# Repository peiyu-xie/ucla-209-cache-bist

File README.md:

# ucla-209-cache-bist

A 32x128-bit fully associative cache with single-cycle CAM tag lookup and an
LFSR/MISR built-in self-test (BIST) engine, taken from RTL to GDSII in 180nm
CMOS and taped out — plus the FPGA tester built to bring the chip up in the
lab. UCLA EC ENGR 209AS/209BS (tapeout course sequence), 2026.

## The chip

| Block | File | What it does |
|---|---|---|
| Cache | `rtl/Cache.sv` | 32 entries x 128-bit data; a CAM priority engine compares every tag in parallel in one cycle |
| BIST controller | `rtl/BIST_Controller.sv` | FSM that sequences write and compare phases over the whole array |
| Test-pattern generator | `rtl/TPG.sv` | LFSR producing pseudo-random write data and addresses |
| Response compactor | `rtl/MISR.sv` | 129-bit multiple-input signature register; the final signature is the pass/fail check |
| Serial I/O | `rtl/P2S.sv`, `rtl/S2P.sv`, `rtl/bidirectional_P2S_S2P.sv` | Moves 128-bit words through the pin-limited pad frame |
| Top | `rtl/Cache_BIST_Top.sv`, `rtl/Chip.sv` | Integration and pad-level top |

**Verification.** Unit- and chip-level SystemVerilog testbenches (`*_tb.sv`)
with randomized address/data stimulus, plus `Chip_post_sim_tb.sv`, a
post-layout gate-level simulation back-annotated with SDF from Innovus.

**Implementation.** Hammer-driven Genus synthesis and Innovus place and route
(MMMC setup in `flow/mmmc_ori.tcl`), DRC/LVS, and post-layout parasitic
extraction before tapeout sign-off.

## The tester (`tester/`)

Silicon validation runs on a Xilinx Zynq board (PYNQ-Z2, `xc7z020clg400-1`).

- **`bus_sequencer.sv`** — 14-state FSM that owns the DUT clock and all
  protocol timing: reset, RUN_BIST, write, compare, and read with bus
  turnaround for the bidirectional data pins. It runs *in the DUT clock
  domain*, so read/write transactions stay cycle-accurate at any test
  frequency, up to the 95 MHz MMCM clock.
- **`tester_top.sv`** — clocking and transport: a 95 MHz MMCM and a
  programmable divider switched glitch-free by a BUFGMUX, the DUT clock
  forwarded off-chip through an ODDR, IOBUFs for the bidirectional bus, and
  synchronizers on the clock-domain crossings of the register interface.
- **`register_map.md`** — the PC-to-FPGA register contract (CTRL, STATUS,
  CLKDIV, ADDR, WDATA0-3, RDATA0-3, ...).
- **`TEST_PROCEDURE.md`** — step-by-step bring-up, first against a chip
  emulator, then against silicon with the same bitstream and commands.
- `tester_top.xdc`, `xdc/chip_emulator.xdc`, `stage1.tcl` — pin constraints and
  Vivado build script.

See `tester/README.md` for build instructions.

## Not included

- `Chip_ckt.v` — Innovus post-layout netlist; it instantiates TSMC standard
  cells (foundry PDK, NDA).
- Course handouts, pad-frame and tapeout documents (instructor / foundry material).
- The chip carrier PCB, which my project partner designed; the tester drives
  its level shifters through `shifter_oe_n` / `shifter_dir`.
- Generated build outputs (bitstreams, Vivado runs).

---

Author: Pei-yu Xie

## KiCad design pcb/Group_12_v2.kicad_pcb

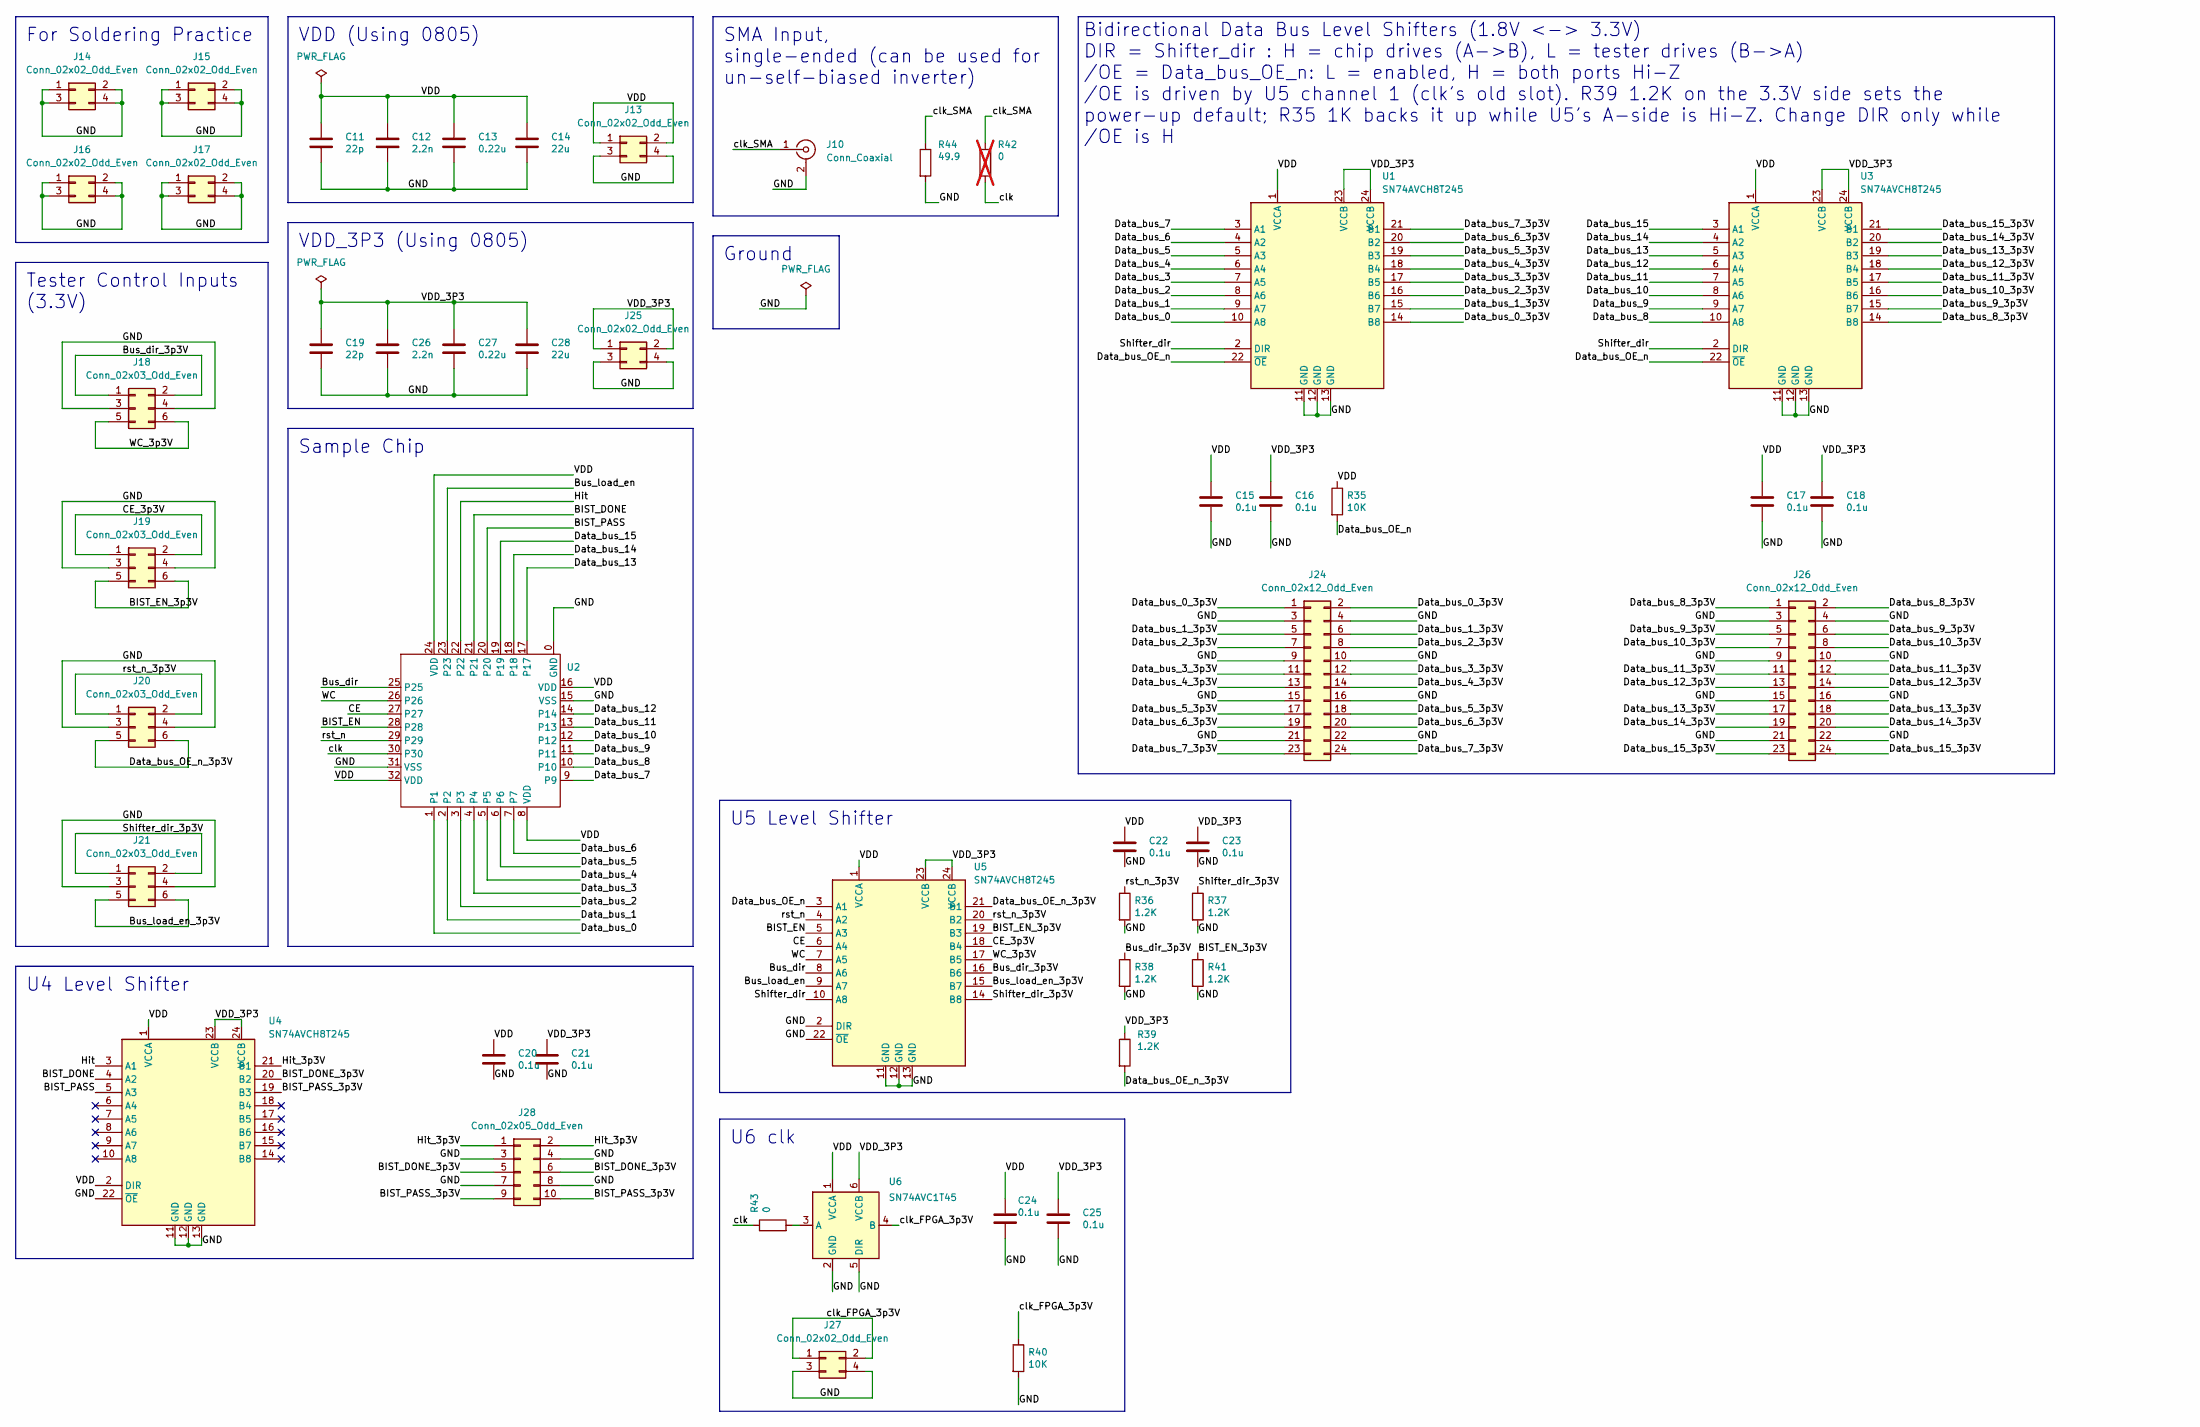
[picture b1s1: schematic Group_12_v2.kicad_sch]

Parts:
C11, C19: 22p; C_0805_2012Metric_Pad1.18x1.45mm_HandSolder; LCSC Part # C1804
C12, C26: 2.2n; C_0805_2012Metric_Pad1.18x1.45mm_HandSolder; LCSC Part # C28260
C13, C27: 0.22u; C_0805_2012Metric_Pad1.18x1.45mm_HandSolder; LCSC Part # C5378
C14, C28: 22u; C_0805_2012Metric_Pad1.18x1.45mm_HandSolder; LCSC Part # C45783
C15, C16, C17, C18, C20, C21, C22, C23, C24, C25: 0.1u; C_0805_2012Metric_Pad1.18x1.45mm_HandSolder; LCSC Part # C1711
J10: Conn_Coaxial; SMA_Samtec_SMA-J-P-H-ST-EM1_EdgeMount
J13, J14, J15, J16, J17, J25, J27: Conn_02x02_Odd_Even; PinHeader_2x02_P2.54mm_Vertical
J18, J19, J20, J21: Conn_02x03_Odd_Even; PinHeader_2x03_P2.54mm_Vertical
J24, J26: Conn_02x12_Odd_Even; PinHeader_2x12_P2.54mm_Vertical
J28: Conn_02x05_Odd_Even; PinHeader_2x05_P2.54mm_Vertical
R35, R40: 10K; R_0805_2012Metric_Pad1.20x1.40mm_HandSolder; LCSC Part # C17414
R36, R37, R38, R39, R41: 1.2K; R_0805_2012Metric_Pad1.20x1.40mm_HandSolder; LCSC Part # C17379
R42: 0; R_0805_2012Metric_Pad1.20x1.40mm_HandSolder; LCSC Part # C17477; not fitted
R43: 0; R_0805_2012Metric_Pad1.20x1.40mm_HandSolder; LCSC Part # C17477
R44: 49.9; R_0805_2012Metric_Pad1.20x1.40mm_HandSolder; LCSC Part # C17720
U1, U3, U4, U5: SN74AVCH8T245; TSSOP-24_4.4x7.8mm_P0.65mm; LCSC Part # C2652945
U2: EE209AS_2026
U6: SN74AVC1T45; SOT-23-6; LCSC Part # C131978

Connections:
/BIST_DONE: U2.21, U4.4 (A2)
/BIST_DONE_3p3V: J28.5, J28.6, U4.20 (B2)
/BIST_EN: U2.28, U5.5 (A3)
/BIST_EN_3p3V: J19.5, J19.6, R41.1, U5.19 (B3)
/BIST_PASS: U2.20, U4.5 (A3)
/BIST_PASS_3p3V: J28.9, J28.10, U4.19 (B3)
/Bus_dir: U2.25, U5.8 (A6)
/Bus_dir_3p3V: J18.1, J18.2, R38.1, U5.16 (B6)
/Bus_load_en: U2.23, U5.9 (A7)
/Bus_load_en_3p3V: J21.5, J21.6, U5.15 (B7)
/CE: U2.27, U5.6 (A4)
/CE_3p3V: J19.1, J19.2, U5.18 (B4)
/Data_bus_0: U1.10 (A8), U2.1
/Data_bus_0_3p3V: J24.1, J24.2, U1.14 (B8)
/Data_bus_1: U1.9 (A7), U2.2
/Data_bus_1_3p3V: J24.5, J24.6, U1.15 (B7)
/Data_bus_2: U1.8 (A6), U2.3
/Data_bus_2_3p3V: J24.7, J24.8, U1.16 (B6)
/Data_bus_3: U1.7 (A5), U2.4
/Data_bus_3_3p3V: J24.11, J24.12, U1.17 (B5)
/Data_bus_4: U1.6 (A4), U2.5
/Data_bus_4_3p3V: J24.13, J24.14, U1.18 (B4)
/Data_bus_5: U1.5 (A3), U2.6
/Data_bus_5_3p3V: J24.17, J24.18, U1.19 (B3)
/Data_bus_6: U1.4 (A2), U2.7
/Data_bus_6_3p3V: J24.19, J24.20, U1.20 (B2)
/Data_bus_7: U1.3 (A1), U2.9
/Data_bus_7_3p3V: J24.23, J24.24, U1.21 (B1)
/Data_bus_8: U2.10, U3.10 (A8)
/Data_bus_8_3p3V: J26.1, J26.2, U3.14 (B8)
/Data_bus_9: U2.11, U3.9 (A7)
/Data_bus_9_3p3V: J26.5, J26.6, U3.15 (B7)
/Data_bus_10: U2.12, U3.8 (A6)
/Data_bus_10_3p3V: J26.7, J26.8, U3.16 (B6)
/Data_bus_11: U2.13, U3.7 (A5)
/Data_bus_11_3p3V: J26.11, J26.12, U3.17 (B5)
/Data_bus_12: U2.14, U3.6 (A4)
/Data_bus_12_3p3V: J26.13, J26.14, U3.18 (B4)
/Data_bus_13: U2.17, U3.5 (A3)
/Data_bus_13_3p3V: J26.17, J26.18, U3.19 (B3)
/Data_bus_14: U2.18, U3.4 (A2)
/Data_bus_14_3p3V: J26.19, J26.20, U3.20 (B2)
/Data_bus_15: U2.19, U3.3 (A1)
/Data_bus_15_3p3V: J26.23, J26.24, U3.21 (B1)
/Data_bus_OE_n: R35.2, U1.22 (~OE), U3.22 (~OE), U5.3 (A1)
/Data_bus_OE_n_3p3V: J20.5, J20.6, R39.2, U5.21 (B1)
/GND: C11.2, C12.2, C13.2, C14.2, C15.2, C16.2, C17.2, C18.2, C19.2, C20.2, C21.2, C22.2, C23.2, C24.2, C25.2, C26.2, C27.2, C28.2, J10.2 (Ext), J13.3, J13.4, J14.1, J14.2, J14.3, J14.4, J15.1, J15.2, J15.3, J15.4, J16.1, J16.2, J16.3, J16.4, J17.1, J17.2, J17.3, J17.4, J18.3, J18.4, J19.3, J19.4, J20.3, J20.4, J21.3, J21.4, J24.3, J24.4, J24.9, J24.10, J24.15, J24.16, J24.21, J24.22, J25.3, J25.4, J26.3, J26.4, J26.9, J26.10, J26.15, J26.16, J26.21, J26.22, J27.3, J27.4, J28.3, J28.4, J28.7, J28.8, R36.2, R37.2, R38.2, R40.2, R41.2, R44.2, U1.11 (GND), U1.12 (GND), U1.13 (GND), U2.0 (GND), U2.15 (VSS), U2.31 (VSS), U3.11 (GND), U3.12 (GND), U3.13 (GND), U4.11 (GND), U4.12 (GND), U4.13 (GND), U4.22 (~OE), U5.2 (DIR), U5.11 (GND), U5.12 (GND), U5.13 (GND), U5.22 (~OE), U6.2 (GND), U6.5 (DIR)
/Hit: U2.22, U4.3 (A1)
/Hit_3p3V: J28.1, J28.2, U4.21 (B1)
/Shifter_dir: U1.2 (DIR), U3.2 (DIR), U5.10 (A8)
/Shifter_dir_3p3V: J21.1, J21.2, R37.1, U5.14 (B8)
/VDD: C11.1, C12.1, C13.1, C14.1, C15.1, C17.1, C20.1, C22.1, C24.1, J13.1, J13.2, R35.1, U1.1 (VCCA), U2.8 (VDD), U2.16 (VDD), U2.24 (VDD), U2.32 (VDD), U3.1 (VCCA), U4.1 (VCCA), U4.2 (DIR), U5.1 (VCCA), U6.1 (VCCA)
/VDD_3P3: C16.1, C18.1, C19.1, C21.1, C23.1, C25.1, C26.1, C27.1, C28.1, J25.1, J25.2, R39.1, U1.23 (VCCB), U1.24 (VCCB), U3.23 (VCCB), U3.24 (VCCB), U4.23 (VCCB), U4.24 (VCCB), U5.23 (VCCB), U5.24 (VCCB), U6.6 (VCCB)
/WC: U2.26, U5.7 (A5)
/WC_3p3V: J18.5, J18.6, U5.17 (B5)
/clk: R42.2, R43.1, U2.30
/clk_FPGA_3p3V: J27.1, J27.2, R40.1, U6.4 (B)
/clk_SMA: J10.1 (In), R42.1, R44.1
/rst_n: U2.29, U5.4 (A2)
/rst_n_3p3V: J20.1, J20.2, R36.1, U5.20 (B2)
unnamed: R43.2, U6.3 (A)

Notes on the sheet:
VDD_3P3 (Using 0805)
VDD (Using 0805)
SMA Input, single-ended (can be used for un-self-biased inverter)
For Soldering Practice
Ground
Sample Chip
U6 clk
U4 Level Shifter
Tester Control Inputs (3.3V)
U5 Level Shifter
Bidirectional Data Bus Level Shifters (1.8V <-> 3.3V) DIR = Shifter_dir : H = chip drives (A->B), L = tester drives (B->A) /OE = Data_bus_OE_n: L = enabled, H = both ports Hi-Z /OE is driven by U5 channel 1 (clk's old slot). R39 1.2K on the 3.3V side sets the power-up default; R35 1K backs it up wh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

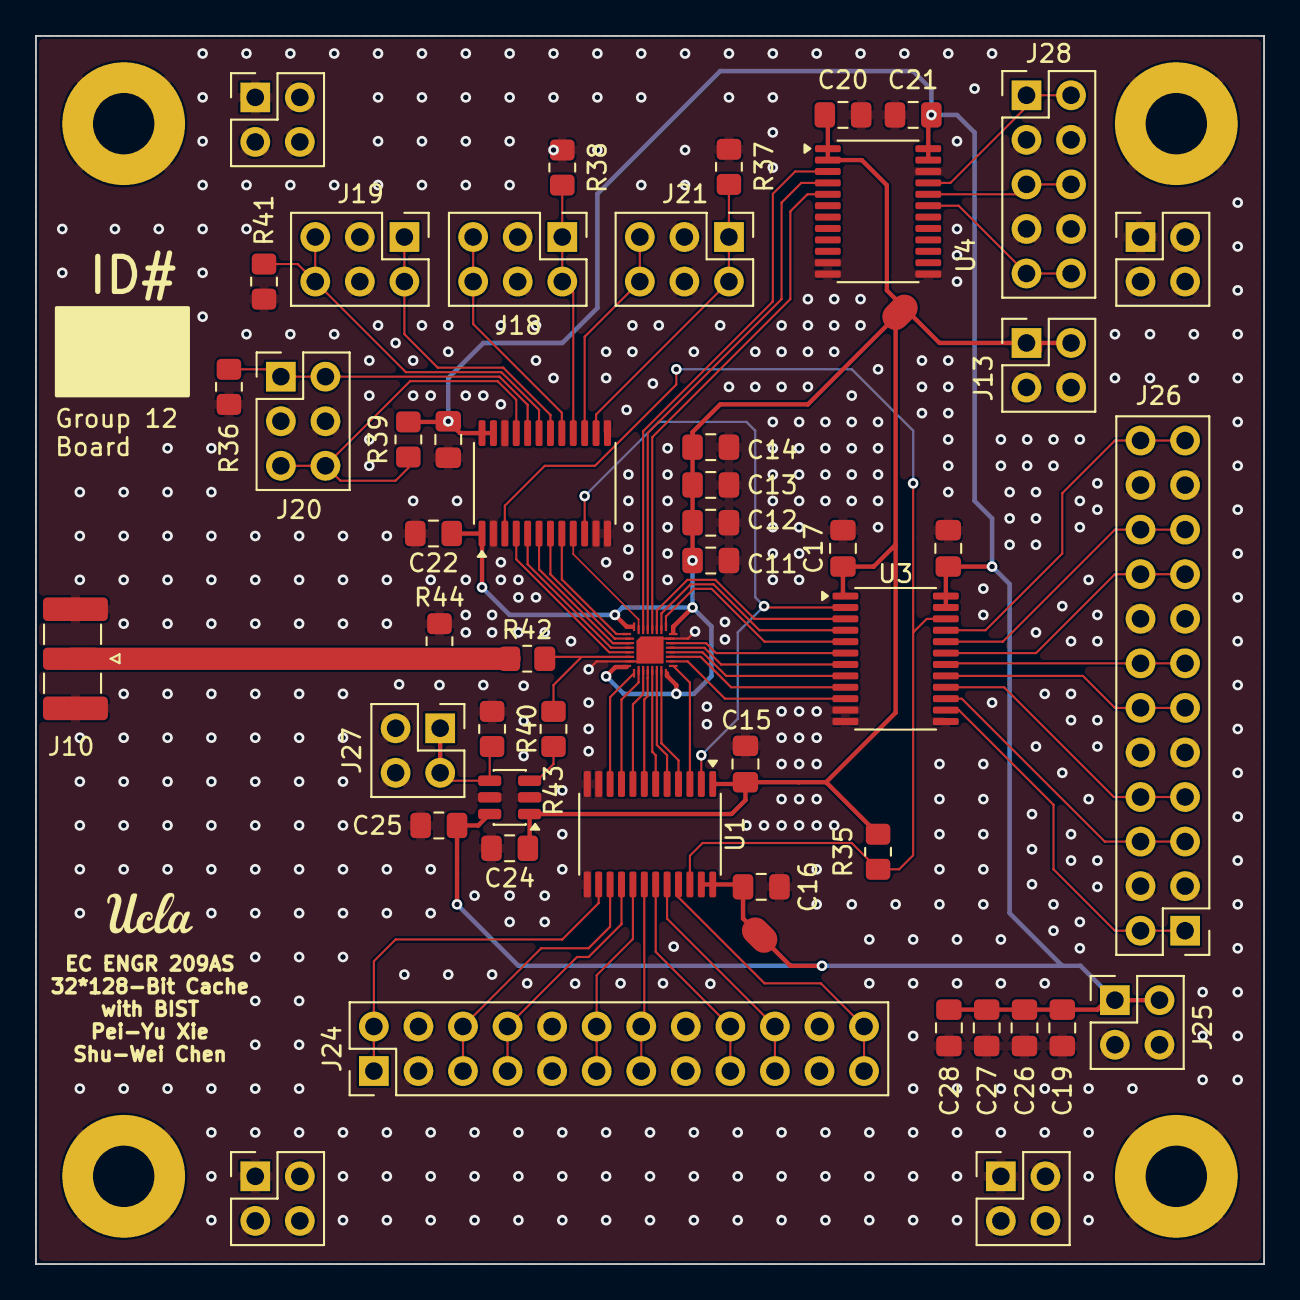
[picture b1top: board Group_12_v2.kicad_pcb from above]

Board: 2 copper layers, 70.0 x 70.0 mm, 49 parts (0 on the bottom side), 61 nets.

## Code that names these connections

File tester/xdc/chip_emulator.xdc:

#=============================================================================
# Chip emulator -- PYNQ-Z2 Raspberry Pi header
#
# Assignment follows the CHIP PAD ORDER (chip pin 1..26) so the Stage-2 DUT
# board routes with almost no crossovers:
#
#   chip  1..16  Data_bus[0..15]  -> RPi  7..33   (ascending, no crossovers)
#   chip 17..21  status/control   -> RPi 35..40   (ascending, no crossovers)
#   chip 22..25  control inputs   -> RPi  3,5,27,28  (the pulled-high pins)
#   chip 26      clk              -> RPi 11       (U7, clock-capable)
#
# The SAME pin assignments apply to the tester board; only the RTL port
# directions differ, so this file can be shared between both projects.
#
# Straight-through 40-pin ribbon, pin N <-> pin N.
# !! Remove the conductors for RPi pins 1, 2, 4, 17 (3V3 / 5V) -- never tie
#    the supplies of two independently powered boards together.
# !! Connect all 8 grounds (RPi pins 6, 9, 14, 20, 25, 30, 34, 39).
#
# RPi pins 10 AND 12 are deliberately LEFT UNASSIGNED, so the clock on pin 11
# has quiet neighbours on BOTH sides in the ribbon.
#
# NOTE on RPi pin 13 (V7): the board XDC omits it (it lists rpio_02..26 +
# sd/sc = 27 GPIO), but the manual says 28 pins are connected, and this was
# settled empirically with rpi_probe -- jumpering 3V3 to header pin 13 drives
# the corresponding probe bit high. V7 IS connected. The board XDC is simply
# missing a line for GPIO27. Every other pin below is verified against
# C:\Xilinx\2025.2\data\boards\board_files\PYNQ-Z2 v1.0.xdc
#
# Also verified on hardware with rpi_probe: RPi pins 3, 5, 27, 28 carry
# PASSIVE pull-ups (each one drives cleanly to 0 when the FPGA sinks it),
# not active drivers. Safe for the four control inputs assigned there.
#
# Pmod A is NOT an alternative: all 8 of its pins (ja[0..7]) are the same FPGA
# balls as RPi pins, including the two pulled-high ID-EEPROM pins. Pmod B
# (W14 Y14 T11 T10 V16 W16 V12 W13) is independent if more I/O is ever needed.
#=============================================================================

#--- Clock (chip pin 26) -----------------------------------------------------
# RPi pin 11 = U7, close to a BUFG (clock-capable). Must carry clk.
set_property -dict {PACKAGE_PIN U7  IOSTANDARD LVCMOS33} [get_ports clk]

# Stage 1 target: 10 MHz. Raise later if you sweep higher.
create_clock -period 100.000 -name dut_clk [get_ports clk]

#--- Data bus (chip pins 1-16) -----------------------------------------------
# All 16 on CLEAN pins so pull behaviour is uniform across the bus.
set_property -dict {PACKAGE_PIN Y18 IOSTANDARD LVCMOS33} [get_ports {Data_bus[0]}]   ;# chip 1  -> RPi 7
set_property -dict {PACKAGE_PIN V6  IOSTANDARD LVCMOS33} [get_ports {Data_bus[1]}]   ;# chip 2  -> RPi 8
set_property -dict {PACKAGE_PIN V7  IOSTANDARD LVCMOS33} [get_ports {Data_bus[2]}]   ;# chip 3  -> RPi 13
set_property -dict {PACKAGE_PIN U8  IOSTANDARD LVCMOS33} [get_ports {Data_bus[3]}]   ;# chip 4  -> RPi 15
set_property -dict {PACKAGE_PIN W6  IOSTANDARD LVCMOS33} [get_ports {Data_bus[4]}]   ;# chip 5  -> RPi 16
set_property -dict {PACKAGE_PIN Y7  IOSTANDARD LVCMOS33} [get_ports {Data_bus[5]}]   ;# chip 6  -> RPi 18
set_property -dict {PACKAGE_PIN V8  IOSTANDARD LVCMOS33} [get_ports {Data_bus[6]}]   ;# chip 7  -> RPi 19
set_property -dict {PACKAGE_PIN V10 IOSTANDARD LVCMOS33} [get_ports {Data_bus[7]}]   ;# chip 8  -> RPi 21
set_property -dict {PACKAGE_PIN F20 IOSTANDARD LVCMOS33} [get_ports {Data_bus[8]}]   ;# chip 9  -> RPi 22
set_property -dict {PACKAGE_PIN W10 IOSTANDARD LVCMOS33} [get_ports {Data_bus[9]}]   ;# chip 10 -> RPi 23
set_property -dict {PACKAGE_PIN F19 IOSTANDARD LVCMOS33} [get_ports {Data_bus[10]}]  ;# chip 11 -> RPi 24
set_property -dict {PACKAGE_PIN U19 IOSTANDARD LVCMOS33} [get_ports {Data_bus[11]}]  ;# chip 12 -> RPi 26
set_property -dict {PACKAGE_PIN Y19 IOSTANDARD LVCMOS33} [get_ports {Data_bus[12]}]  ;# chip 13 -> RPi 29
set_property -dict {PACKAGE_PIN U18 IOSTANDARD LVCMOS33} [get_ports {Data_bus[13]}]  ;# chip 14 -> RPi 31
set_property -dict {PACKAGE_PIN B20 IOSTANDARD LVCMOS33} [get_ports {Data_bus[14]}]  ;# chip 15 -> RPi 32
set_property -dict {PACKAGE_PIN W8  IOSTANDARD LVCMOS33} [get_ports {Data_bus[15]}]  ;# chip 16 -> RPi 33

# The bus genuinely floats during turnaround (neither side drives for a cycle).
# A KEEPER holds the last driven value -- prevents a mid-rail float without
# fighting either driver, and without ever faking plausible-looking data.
set_property PULLTYPE KEEPER [get_ports {Data_bus[*]}]

#--- Status outputs + bus control (chip pins 17-21) --------------------------
# BIST_PASS deliberately on a CLEAN pin: a pull-up would make a broken or
# disconnected pin read PASS, hiding a dead chip.
# Bus_dir likewise clean: floating high would make the chip drive the bus.
set_property -dict {PACKAGE_PIN Y8  IOSTANDARD LVCMOS33} [get_ports BIST_PASS]    ;# chip 17 -> RPi 35
set_property -dict {PACKAGE_PIN B19 IOSTANDARD LVCMOS33} [get_ports BIST_DONE]    ;# chip 18 -> RPi 36
set_property -dict {PACKAGE_PIN W9  IOSTANDARD LVCMOS33} [get_ports Hit]          ;# chip 19 -> RPi 37
set_property -dict {PACKAGE_PIN A20 IOSTANDARD LVCMOS33} [get_ports Bus_load_en]  ;# chip 20 -> RPi 38
set_property -dict {PACKAGE_PIN Y9  IOSTANDARD LVCMOS33} [get_ports Bus_dir]      ;# chip 21 -> RPi 40

# ONE BITSTREAM FOR BOTH TEST STAGES.
# In the 7-wire BIST stage these two are not connected, and Chip.sv uses them
# outside the BIST mux (dir <= Bus_dir; load_en <= Bus_load_en), so they would
# float -- a mid-rail CMOS input draws crowbar current, and dir=1 would make
# the chip drive Data_bus unbidden.
#
# A weak internal pull-down parks both LOW when unwired. Once the full 26-wire
# harness is connected the tester's output overcomes it easily, so the same
# bitstream serves BIST and normal-mode testing with no rebuild.
#
# CE and WC need no equivalent: Cache_BIST_Top muxes them out whenever
# BIST_EN is high, so their floating state during BIST is harmless.
set_property PULLTYPE PULLDOWN [get_ports Bus_dir]
set_property PULLTYPE PULLDOWN [get_ports Bus_load_en]

#--- Control inputs (chip pins 22-25) ----------------------------------------
# These four sit on the board's PULLED-HIGH pins (RPi 3, 5, 27, 28).
# Safe here: all are actively driven by the tester, and their default-high
# state before configuration is benign (rst_n high = not reset).
set_property -dict {PACKAGE_PIN W18 IOSTANDARD LVCMOS33} [get_ports WC]           ;# chip 22 -> RPi 3  (pull-high)
set_property -dict {PACKAGE_PIN W19 IOSTANDARD LVCMOS33} [get_ports CE]           ;# chip 23 -> RPi 5  (pull-high)
set_property -dict {PACKAGE_PIN Y16 IOSTANDARD LVCMOS33} [get_ports BIST_EN]      ;# chip 24 -> RPi 27 (pull-high)
set_property -dict {PACKAGE_PIN Y17 IOSTANDARD LVCMOS33} [get_ports rst_n]        ;# chip 25 -> RPi 28 (pull-high)

#--- Unused pins -------------------------------------------------------------
# Leave unused I/O high-Z rather than driven, so nothing contends on the ribbon.
set_property BITSTREAM.CONFIG.UNUSEDPIN PULLNONE [current_design]

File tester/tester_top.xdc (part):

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# they cannot drive against the chip while Chip.sv's registered dir is still
# catching up. Unused in Stage 1; routed now so the PCB can rely on it.
# Both shifter controls are on the RPi header (pins 10 and 12) -- see below.
set_property -dict {PACKAGE_PIN C20 IOSTANDARD LVCMOS33} [get_ports shifter_oe_n]  ;# RPi 12 -> PCB J20.5 Data_bus_OE_n_3p3V
# U1/U3 DIR (PCB net Shifter_dir_3p3V): 1 = chip drives the bus, 0 = tester.
# The PCB pulls it low (R37), i.e. tester -> chip, when this pin is not driven.
set_property -dict {PACKAGE_PIN Y6  IOSTANDARD LVCMOS33} [get_ports shifter_dir]   ;# RPi 10 -> PCB J21.1 Shifter_dir_3p3V

#--- DUT clock out (chip pin 26) ---------------------------------------------
set_property -dict {PACKAGE_PIN U7  IOSTANDARD LVCMOS33} [get_ports dut_clk]       ;# RPi 11  clock-capable
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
